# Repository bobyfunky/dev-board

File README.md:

###dev-board

#Add led tester / improve switches

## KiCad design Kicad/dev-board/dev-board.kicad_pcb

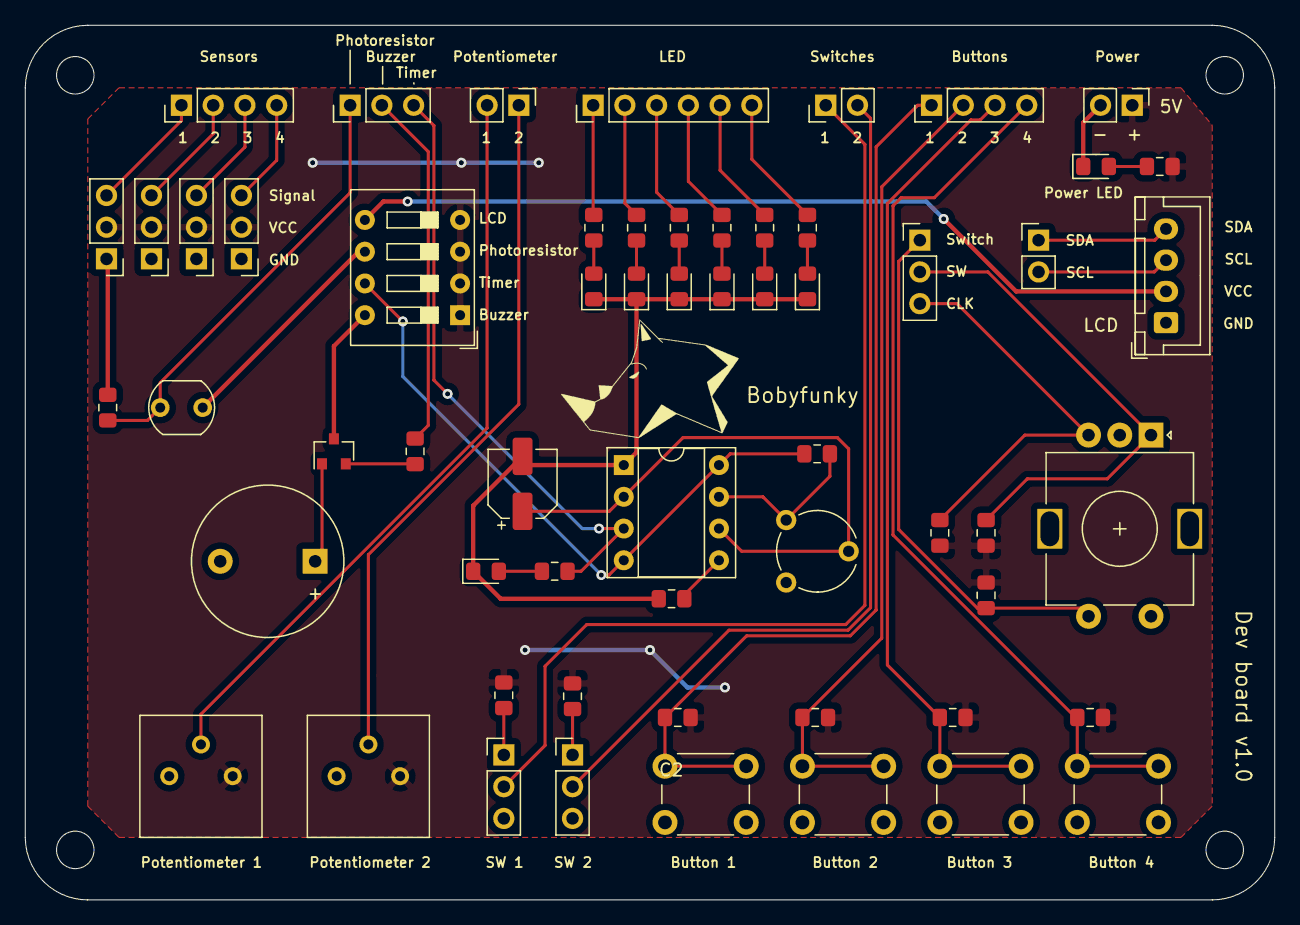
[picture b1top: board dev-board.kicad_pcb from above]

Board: 2 copper layers, 100.0 x 70.0 mm, 59 parts (0 on the bottom side), 47 nets.

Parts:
BZ1: Buzzer; Buzzer_12x9.5RM7.6
C1: CP; CP_Elec_5x5.3
C2: C; C_0805_2012Metric_Pad1.15x1.40mm_HandSolder
D1, D2, D3, D4, D5, D6, D7, D8: LED; LED_0805_2012Metric_Pad1.15x1.40mm_HandSolder
J1, J8, J9, J10, J11, J15: Conn_01x03_Male; PinHeader_1x03_P2.54mm_Vertical
J2: Conn_01x04_Male; JST_XH_B4B-XH-A_1x04_P2.50mm_Vertical
J3, J4, J5, J6: Conn_01x02_Male; PinHeader_1x02_P2.54mm_Vertical
J7, J13: Conn_01x04_Male; PinHeader_1x04_P2.54mm_Vertical
J16: Conn_01x06_Male; PinHeader_1x06_P2.54mm_Vertical
Q1: 2N2219; SOT-23
R1, R2, R3, R4, R6, R7, R8, R9, R10, R11, R12, R13, R14, R15, R16, R17, R18, R19, R20, R21: R; R_0805_2012Metric_Pad1.15x1.40mm_HandSolder
R5: A1050; R_LDR_5.1x4.3mm_P3.4mm_Vertical
RV1, RV2: R_POT; Potentiometer_Bourns_3386P_Vertical
RV3: R_POT; Potentiometer_Piher_PT-6-V_Vertical
SW1: SW_DIP_x04; SW_DIP_SPSTx04_Slide_9.78x12.34mm_W7.62mm_P2.54mm
SW2, SW3: SW_SPDT; PinHeader_1x03_P2.54mm_Vertical
SW4, SW5, SW6, SW7: SW_Push; SW_PUSH_6mm_H5mm
SW8: Rotary_Encoder_Switch; RotaryEncoder_Alps_EC11E-Switch_Vertical_H20mm
U1: NE555P; DIP-8_W7.62mm_Socket

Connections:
/buzzer: Q1.3, SW1.8
/lcd: J2.2, SW1.5
/light_sensor: R5.1, SW1.6
/light_sensor_pin: J1.1, R5.2, R6.2
/timer: R12.2, SW1.7, U1.4, U1.8
/timer_pin: J1.3, R11.2, U1.3
GND: BZ1.2, C1.2, C2.2, D1.1, D2.1, D3.1, D4.1, D5.1, D6.1, D7.1, D8.1, J2.1, J3.2, J8.1, J9.1, J10.1, J11.1, R6.1, RV1.3, RV2.3, SW2.3, SW3.3, SW4.2, SW5.2, SW6.2, SW7.2, SW8.C, SW8.S2, U1.1
unnamed: BZ1.1, Q1.1
unnamed: C1.1, RV3.2, U1.2, U1.6
unnamed: C2.1, U1.5
unnamed: D1.2, R2.1
unnamed: D2.2, R11.1
unnamed: D3.2, R14.2
unnamed: D4.2, R15.2
unnamed: D5.2, R16.2
unnamed: D6.2, R17.2
unnamed: D7.2, R18.2
unnamed: D8.2, R19.2
unnamed: J1.2, R1.2
unnamed: J2.3, J5.2
unnamed: J2.4, J5.1
unnamed: J4.1, RV2.2
unnamed: J4.2, RV1.2
unnamed: J6.1, SW3.2
unnamed: J6.2, SW2.2
unnamed: J7.1, J8.3
unnamed: J7.2, J9.3
unnamed: J7.3, J10.3
unnamed: J7.4, J11.3
unnamed: J13.1, R10.2, SW4.1
unnamed: J13.2, R9.2, SW5.1
unnamed: J13.3, R8.2, SW6.1
unnamed: J13.4, R7.2, SW7.1
unnamed: J15.1, R13.2, SW8.S1
unnamed: J15.2, R20.2, SW8.A
unnamed: J15.3, R21.2, SW8.B
unnamed: J16.1, R14.1
unnamed: J16.2, R15.1
unnamed: J16.3, R16.1
unnamed: J16.4, R17.1
unnamed: J16.5, R18.1
unnamed: J16.6, R19.1
unnamed: Q1.2, R1.1
unnamed: R3.2, SW3.1
unnamed: R4.2, SW2.1
unnamed: R12.1, RV3.3, U1.7
VCC: J3.1, J8.2, J9.2, J10.2, J11.2, R2.2, R3.1, R4.1, R7.1, R8.1, R9.1, R10.1, R13.1, R20.1, R21.1, RV1.1, RV2.1, SW1.1, SW1.2, SW1.3, SW1.4

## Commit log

2020-09-07 Init repo
2020-09-08 Add 555 timer + DIP switches
2020-09-14 Assign Footprint
2020-09-19 PCB final step
2020-09-21 Drill holes
2020-10-18 Add components values
